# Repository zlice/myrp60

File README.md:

# RP2040 60% keyboard

60% keyboard with my preferred bottom/right layout.

Uses hacky wiring to save rows and push keys into other cols. This makes for a semi-weird layout in the keymap but it works fine.

# Kicad /jlcpcb

Everything is on one side so it is cheaper to fab and so you do not see chips or didodes.

- File > Fabcrication outputs > component placement (to /tmp/fireball-components)
- `./kicad_pos_to_cpl.py /tmp/myrp60-components/myrp60-top-pos.csv /tmp/myrp60-jlcpcb-placement-pos.cmp.csv` (not in repo)

# Build / Flash

`cp qmk/myrp60 <qmk_path>/keyboard`

`CFLAGS="-Wno-error=deprecated -Wp,-w" make myrp60`

mount and copy to rp2040 drive

# Shoutouts

- Jfedor for the PCB - https://github.com/jfedor2/rp2040-pmw3360
- QMK for the software/firmware and helpful community
- wokwi for the placement script - https://github.com/wokwi/kicad-jlcpcb-bom-plugin

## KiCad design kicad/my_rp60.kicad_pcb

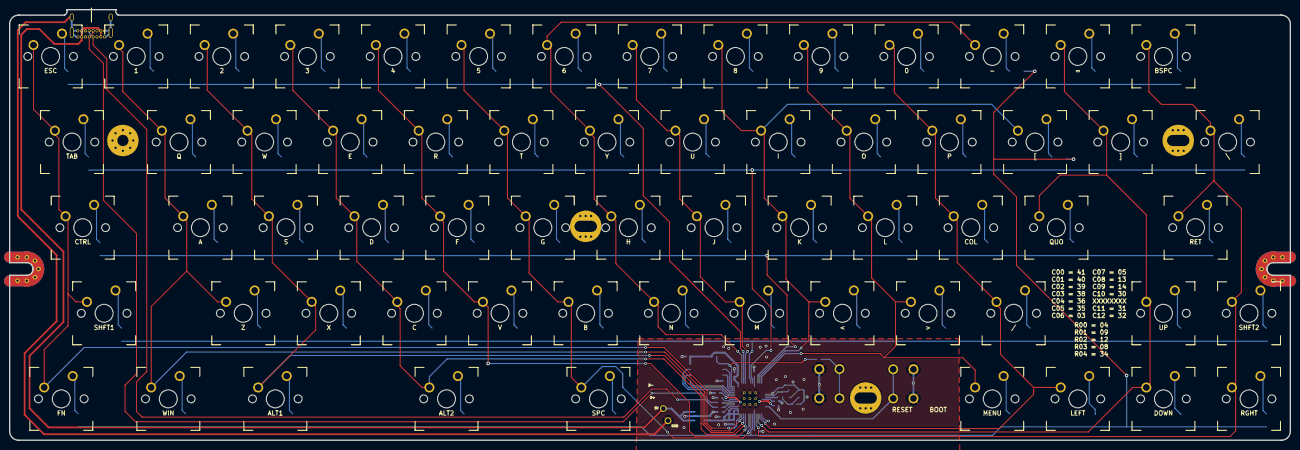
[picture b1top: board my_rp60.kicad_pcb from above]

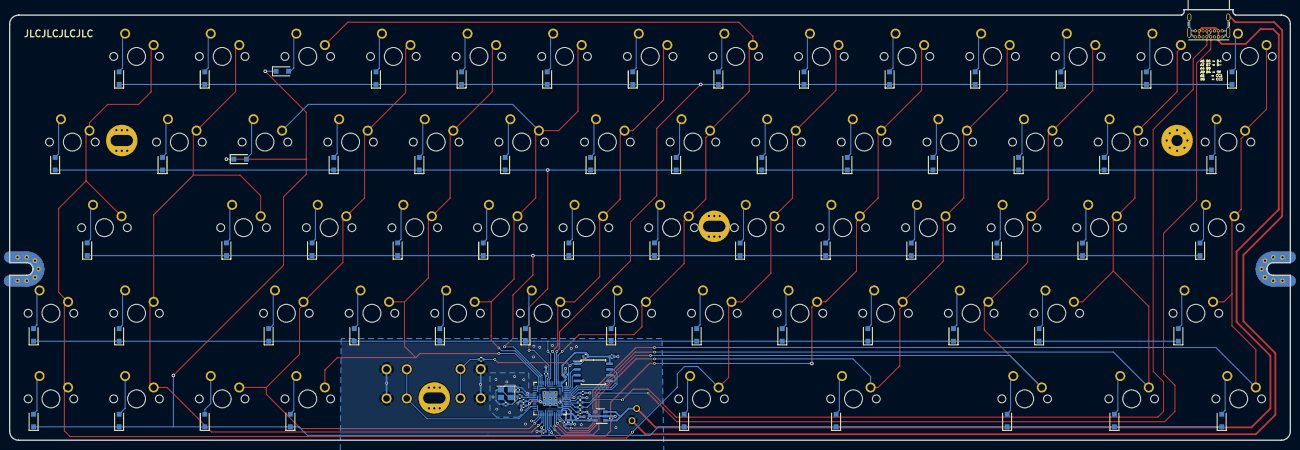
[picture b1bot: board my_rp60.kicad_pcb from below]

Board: 2 copper layers, 285.0 x 95.8 mm, 152 parts (89 on the bottom side), 36 nets.

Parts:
0, 1, 2, 3, 4, 5, 6, 7, 8, 9: SW_Cherry_MX_1.00u_PCB
-: SW_Cherry_MX_1.00u_PCB
/: SW_Cherry_MX_1.00u_PCB
<: SW_Cherry_MX_1.00u_PCB
=: SW_Cherry_MX_1.00u_PCB
>: SW_Cherry_MX_1.00u_PCB
A: SW_Cherry_MX_1.00u_PCB
ALT1, ALT2: MX-1.25U-NoLED
B: SW_Cherry_MX_1.00u_PCB
BSPC: SW_Cherry_MX_1.00u_PCB
C: SW_Cherry_MX_1.00u_PCB
C1, C2, C3, C4, C5, C6, C7, C8, C9, C17: 100n; C_0402_1005Metric
C10, C13, C15, C16: 1u; C_0402_1005Metric
C18, C19: 30p; C_0402_1005Metric
COL: SW_Cherry_MX_1.00u_PCB
CTRL: MX-1.75U-NoLED
D: SW_Cherry_MX_1.00u_PCB
DOWN: SW_Cherry_MX_1.00u_PCB
D_0, D_1, D_2, D_3, D_4, D_5, D_6, D_7, D_8, D_9: D_SOD-123F
D_-: D_SOD-123F
D_/: D_SOD-123F
D_<: D_SOD-123F
D_=: D_SOD-123F
D_>: D_SOD-123F
D_A: D_SOD-123F
D_ALT1, D_ALT2: D_SOD-123F
D_B: D_SOD-123F
D_BSPC: D_SOD-123F
D_C: D_SOD-123F
D_COL: D_SOD-123F
D_CTRL: D_SOD-123F
D_D: D_SOD-123F
D_DOWN: D_SOD-123F
D_E: D_SOD-123F
D_ESC: D_SOD-123F
D_F: D_SOD-123F
D_FN: D_SOD-123F
D_G: D_SOD-123F
D_H: D_SOD-123F
D_I: D_SOD-123F
D_J: D_SOD-123F
D_K: D_SOD-123F
D_L: D_SOD-123F
D_LEFT: D_SOD-123F
D_M: D_SOD-123F
D_MENU: D_SOD-123F
D_N: D_SOD-123F
D_O: D_SOD-123F
D_P: D_SOD-123F
D_Q: D_SOD-123F
D_QUO: D_SOD-123F
D_R: D_SOD-123F
D_RET: D_SOD-123F
D_RGHT: D_SOD-123F
D_S: D_SOD-123F
D_SHFT1, D_SHFT2: D_SOD-123F
D_SPC: D_SOD-123F
D_T: D_SOD-123F
D_TAB: D_SOD-123F
D_U: D_SOD-123F
D_UP: D_SOD-123F
D_V: D_SOD-123F
D_W: D_SOD-123F
D_WIN: D_SOD-123F
D_X: D_SOD-123F
D_Y: D_SOD-123F
D_Z: D_SOD-123F
D_[: D_SOD-123F
D_\: D_SOD-123F
D_]: D_SOD-123F
E: SW_Cherry_MX_1.00u_PCB
ESC: SW_Cherry_MX_1.00u_PCB
F: SW_Cherry_MX_1.00u_PCB
FN: MX-1.25U-NoLED
G: SW_Cherry_MX_1.00u_PCB
H: SW_Cherry_MX_1.00u_PCB
I: SW_Cherry_MX_1.00u_PCB
J: SW_Cherry_MX_1.00u_PCB
K: SW_Cherry_MX_1.00u_PCB
L: SW_Cherry_MX_1.00u_PCB
LEFT: SW_Cherry_MX_1.00u_PCB
M: SW_Cherry_MX_1.00u_PCB
MENU: SW_Cherry_MX_1.00u_PCB
N: SW_Cherry_MX_1.00u_PCB
O: SW_Cherry_MX_1.00u_PCB
P: SW_Cherry_MX_1.00u_PCB
Q: SW_Cherry_MX_1.00u_PCB
QUO: SW_Cherry_MX_1.00u_PCB
R: SW_Cherry_MX_1.00u_PCB
R3, R4: 27; R_0402_1005Metric
R5: 10k; R_0402_1005Metric
R6, R7: 1k; R_0402_1005Metric
RET: MX-2.25U-NoLED
RGHT: SW_Cherry_MX_1.00u_PCB
S: SW_Cherry_MX_1.00u_PCB
SHFT1: MX-2.25U-NoLED
SHFT2: SW_Cherry_MX_1.00u_PCB
SPC: MX-2U-NoLED
T: SW_Cherry_MX_1.00u_PCB
TAB: MX-1.5U-NoLED
U: SW_Cherry_MX_1.00u_PCB
U3: RP2040; RP2040-QFN-56
U4: TLV73333PDBV; SOT-23-5
U5: W25Q128JVS; SOIC-8_5.23x5.23mm_P1.27mm
UP: SW_Cherry_MX_1.00u_PCB
USB: USB_C_Receptacle_GCT_USB4085
V: SW_Cherry_MX_1.00u_PCB
W: SW_Cherry_MX_1.00u_PCB
WIN: MX-1.25U-NoLED
X: SW_Cherry_MX_1.00u_PCB
Y: SW_Cherry_MX_1.00u_PCB
Y1: Crystal_GND24; Crystal_SMD_3225-4Pin_3.2x2.5mm
Z: SW_Cherry_MX_1.00u_PCB
[: SW_Cherry_MX_1.00u_PCB
\: MX-1.5U-NoLED
]: SW_Cherry_MX_1.00u_PCB

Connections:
3: D_M.2, M.2
+1V1: C1.1, C2.1, C13.1, U3.23, U3.45, U3.50
+3V3: C3.1, C4.1, C5.1, C6.1, C7.1, C8.1, C9.1, C10.1, C16.1, C17.1, R5.1, U3.1, U3.10, U3.22, U3.33, U3.42, U3.43, U3.44, U3.48, U3.49, U4.5, U5.8
+5V: C15.1, U4.1, U4.3
D+: R3.1, USB.A6
D-: R4.1, USB.A7
GND: C1.2, C2.2, C3.2, C4.2, C6.2, C7.2, C8.2, C9.2, C10.2, C13.2, C15.2, C16.2, C17.2, C18.1, C19.2, U3.19, U3.57, U4.2, U5.4, Y1.2, Y1.4
unnamed: C19.1, R7.1, Y1.3
unnamed: R3.2, U3.47
unnamed: R4.2, U3.46
QSPI_SCLK: U3.52, U5.6
QSPI_SD0: U3.53, U5.5
QSPI_SD1: U3.55, U5.2
QSPI_SD2: U3.54, U5.3
QSPI_SD3: U3.51, U5.7
QSPI_SS: R5.2, R6.1, U3.56, U5.1
XIN: C18.2, U3.20, Y1.1
XOUT: R7.2, U3.21
c0: CTRL.1, ESC.1, FN.1, SHFT1.1, TAB.1, U3.41
c1: 1.1, A.1, Q.1, U3.40, WIN.1, Z.1
c2: 2.1, ALT1.1, S.1, U3.39, W.1, X.1
c3: 3.1, ALT2.1, C.1, D.1, E.1, U3.38
c4: 4.1, F.1, R.1, U3.36, V.1
c5: 5.1, B.1, G.1, SPC.1, T.1, U3.35
c6: 6.1, -.1, H.1, N.1, U3.3, Y.1
c7: 7.1, J.1, M.1, U.1, U3.5
c8: 8.1, <.1, I.1, K.1, U3.13, [.1
c9: 9.1, >.1, L.1, MENU.1, O.1, U3.14
c10: 0.1, /.1, COL.1, LEFT.1, P.1, U3.30
c11: =.1, DOWN.1, QUO.1, U3.31, UP.1, ].1
c12: BSPC.1, RET.1, RGHT.1, SHFT2.1, U3.32, \.1
r0: 0.2, 1.2, 2.2, 3.2, 4.2, 6.2, 7.2, 8.2, 9.2, =.2, BSPC.2, D_0.1, D_1.1, D_2.1, D_3.1, D_4.1, D_5.1, D_6.1, D_7.1, D_7.2, D_8.1, D_9.1, D_=.1, D_BSPC.1, D_ESC.1, ESC.2, U3.4
r1: D_E.1, D_I.1, D_O.1, D_P.1, D_Q.1, D_R.1, D_T.1, D_TAB.1, D_U.1, D_W.1, D_Y.1, D_\.1, D_\.2, D_].1, D_].2, E.2, I.2, O.2, P.2, Q.2, R.2, T.2, TAB.2, U.2, U3.9, W.2, Y.2, \.2, ].2
r2: A.2, COL.2, CTRL.2, D.2, D_A.1, D_A.2, D_COL.1, D_COL.2, D_CTRL.1, D_CTRL.2, D_D.1, D_D.2, D_F.1, D_F.2, D_G.1, D_G.2, D_H.1, D_H.2, D_J.1, D_J.2, D_K.1, D_K.2, D_L.1, D_L.2, D_QUO.1, D_QUO.2, D_RET.1, D_RET.2, D_S.1, D_S.2, F.2, G.2, H.2, J.2, K.2, L.2, QUO.2, RET.2, S.2, U3.12
r3: /.2, <.2, >.2, B.2, C.2, D_/.1, D_/.2, D_<.1, D_<.2, D_>.1, D_>.2, D_B.1, D_B.2, D_C.1, D_C.2, D_M.1, D_N.1, D_N.2, D_SHFT1.1, D_SHFT1.2, D_SHFT2.1, D_SHFT2.2, D_UP.1, D_UP.2, D_V.1, D_V.2, D_X.1, D_X.2, D_Z.1, D_Z.2, N.2, SHFT1.2, SHFT2.2, U3.8, UP.2, V.2, X.2, Z.2
r4: -.2, ALT1.2, ALT2.2, DOWN.2, D_-.2, D_ALT1.1, D_ALT1.2, D_ALT2.1, D_ALT2.2, D_DOWN.1, D_DOWN.2, D_FN.1, D_FN.2, D_LEFT.1, D_LEFT.2, D_MENU.1, D_MENU.2, D_RGHT.1, D_RGHT.2, D_SPC.1, D_SPC.2, D_WIN.1, D_WIN.2, D_[.2, FN.2, LEFT.2, MENU.2, RGHT.2, SPC.2, U3.34, WIN.2, [.2

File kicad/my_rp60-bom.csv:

Id,Designator,Footprint,Quantity,Designation,Supplier and ref
1,"C2,C4,C5,C9,C8,C6,C7,C1,C17,C3",C_0402_1005Metric,10,100n,C1525
2,"C15,C13,C16,C10",C_0402_1005Metric,4,1u,C52923
3,"C19,C18",C_0402_1005Metric,2,30p,C1570
4,U5,SOIC-8_5.23x5.23mm_P1.27mm,1,W25Q128JVS,C97521
5,"R6,R7",R_0402_1005Metric,2,1k,C11702
6,U3,RP2040-QFN-56,1,RP2040,C2040
7,"R4,R3",R_0402_1005Metric,2,27,C138021
8,Y1,Crystal_SMD_3225-4Pin_3.2x2.5mm,1,Crystal_GND24,C9002
9,"SW2,SW1",SW_SPST_Omron_B3FS-100xP,2,SW_Push,C271750
10,R5,R_0402_1005Metric,1,10k,C25744
11,U4,SOT-23-5,1,TLV73333PDBV,C134139

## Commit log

2024-01-07 init
2024-01-29 limit power and set polling rate
2024-02-07 fix KC_NO nokey layout
2024-04-21 qmk: update code to own keyboard dir
2024-11-02 kicad: oneside pcb
